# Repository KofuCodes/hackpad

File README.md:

# TetriPad
This is a project I made for Highway called the Tetripad a custom hackpad built to play Tetris with precision and style! It features 4 switches arranged in a pyramid layout, just like the classic D-pad, making movement super intuitive. I designed it to give me fast, reliable control for games like Tetris, especially when regular keyboards just don't cut it. It also has an OLED screen that responds to my inputs, which makes it feel way more interactive and alive. This is one of my first full firmware + hardware projects, and it’s been a blast combining code, wiring, and gameplay into one neat little build. I’m excited to keep building more projects like this and push what I can do even further!<br/>

# Schematic and PCB

Imagine the case with tetris colours...

# Components
4x Cherry MX Switches<br/>
4x SK6812 MINI Leds<br/>
1x XIAO RP2040<br/>
1x 0.91 inch OLED displays<br/>
4x Keycaps<br/>
Custom 3D Printed Top Case<br/>
Custom 3D Printed Bottom Case<br/>

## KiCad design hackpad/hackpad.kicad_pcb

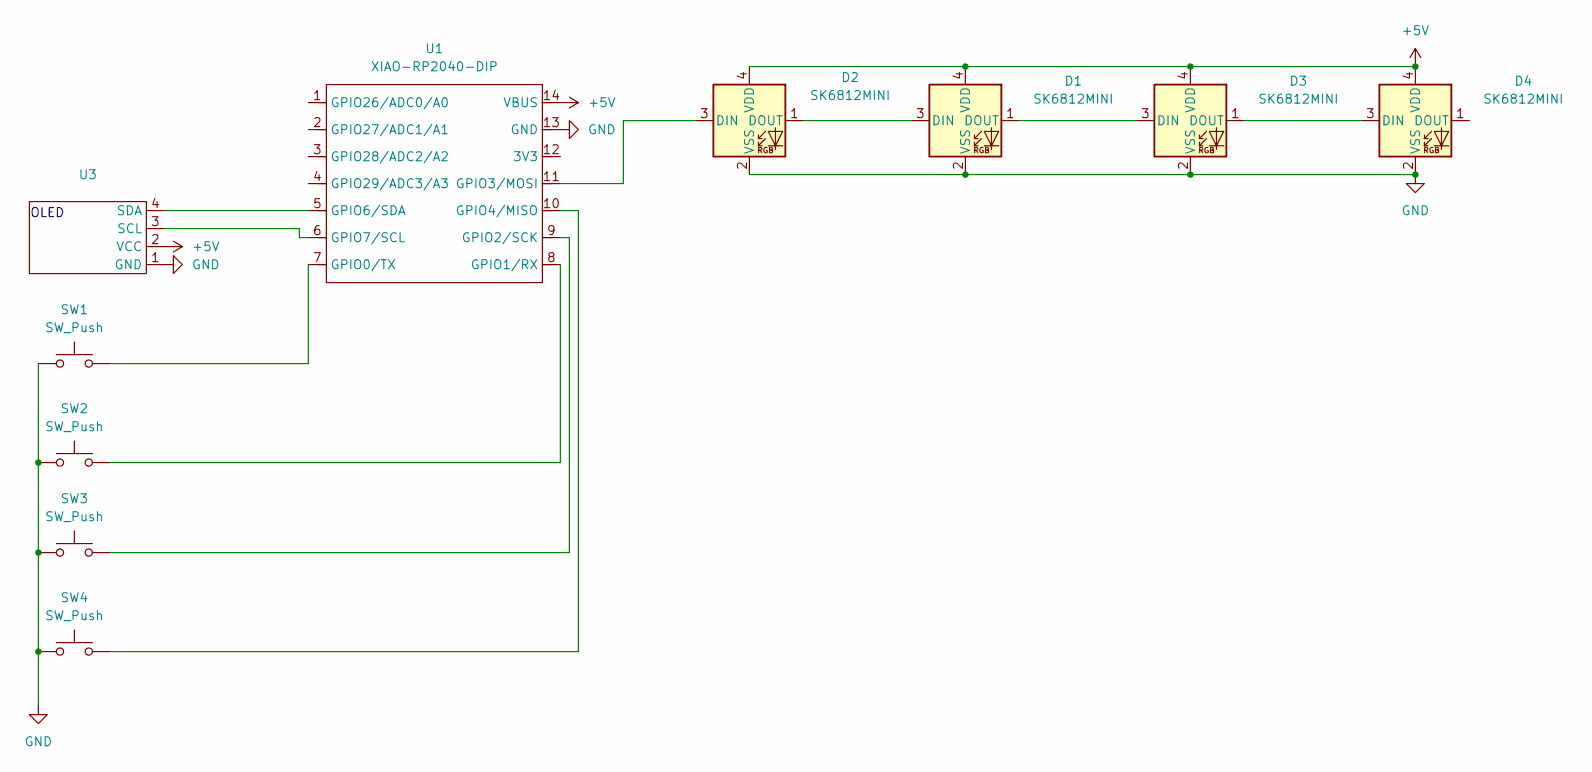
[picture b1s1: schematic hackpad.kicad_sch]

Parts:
D1, D2, D3, D4: SK6812MINI; LED_SK6812MINI_PLCC4_3.5x3.5mm_P1.75mm
SW1, SW2, SW3, SW4: SW_Push; SW_Cherry_MX_1.00u_PCB
U1: XIAO-RP2040-DIP
U3: SSD1306-0.91-OLED-4pin-128x32

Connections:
+5V: D1.4 (VDD), D2.4 (VDD), D3.4 (VDD), D4.4 (VDD), U1.14 (VBUS), U3.2 (VCC)
GND: D1.2 (VSS), D2.2 (VSS), D3.2 (VSS), D4.2 (VSS), SW1.1, SW2.1, SW3.1, SW4.1, U1.13 (GND), U3.1 (GND)
unnamed: D1.3 (DIN), D2.1 (DOUT)
unnamed: D1.1 (DOUT), D3.3 (DIN)
unnamed: D2.3 (DIN), U1.11 (GPIO3/MOSI)
unnamed: D3.1 (DOUT), D4.3 (DIN)
unnamed: SW1.2, U1.7 (GPIO0/TX)
unnamed: SW2.2, U1.8 (GPIO1/RX)
unnamed: SW3.2, U1.9 (GPIO2/SCK)
unnamed: SW4.2, U1.10 (GPIO4/MISO)
unnamed: U1.5 (GPIO6/SDA), U3.4 (SDA)
unnamed: U1.6 (GPIO7/SCL), U3.3 (SCL)

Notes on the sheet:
OLED

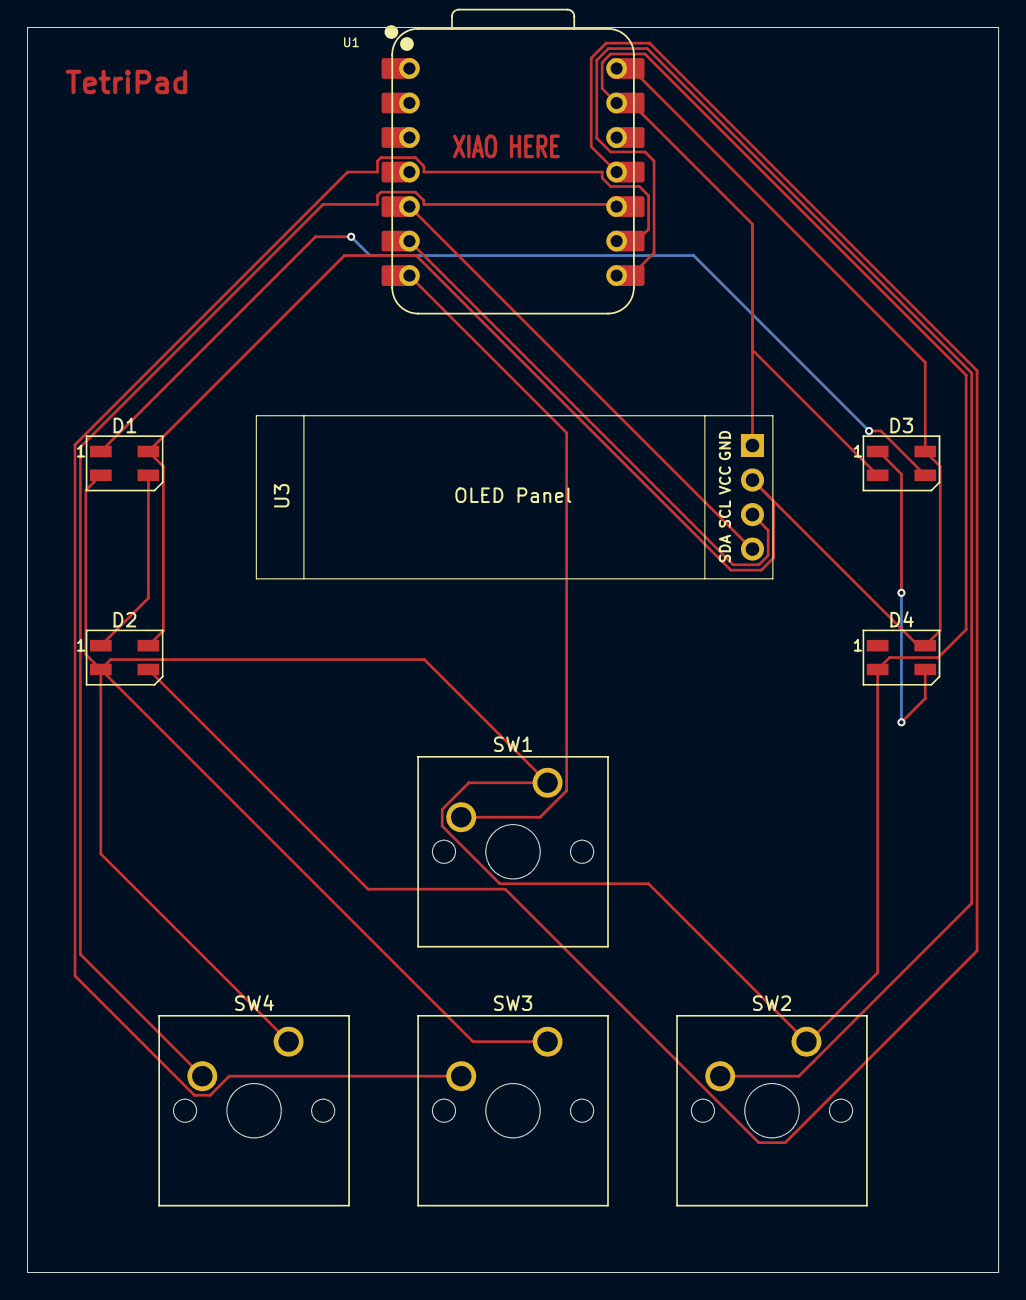
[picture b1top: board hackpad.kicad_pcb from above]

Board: 2 copper layers, 71.4 x 91.6 mm, 10 parts (0 on the bottom side), 12 nets.

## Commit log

2025-06-06 init
2025-06-12 update (06/11/2025)
    -finished schematic
    -finished pcb design
2025-06-27 added BOM
2025-06-27 organization fix
